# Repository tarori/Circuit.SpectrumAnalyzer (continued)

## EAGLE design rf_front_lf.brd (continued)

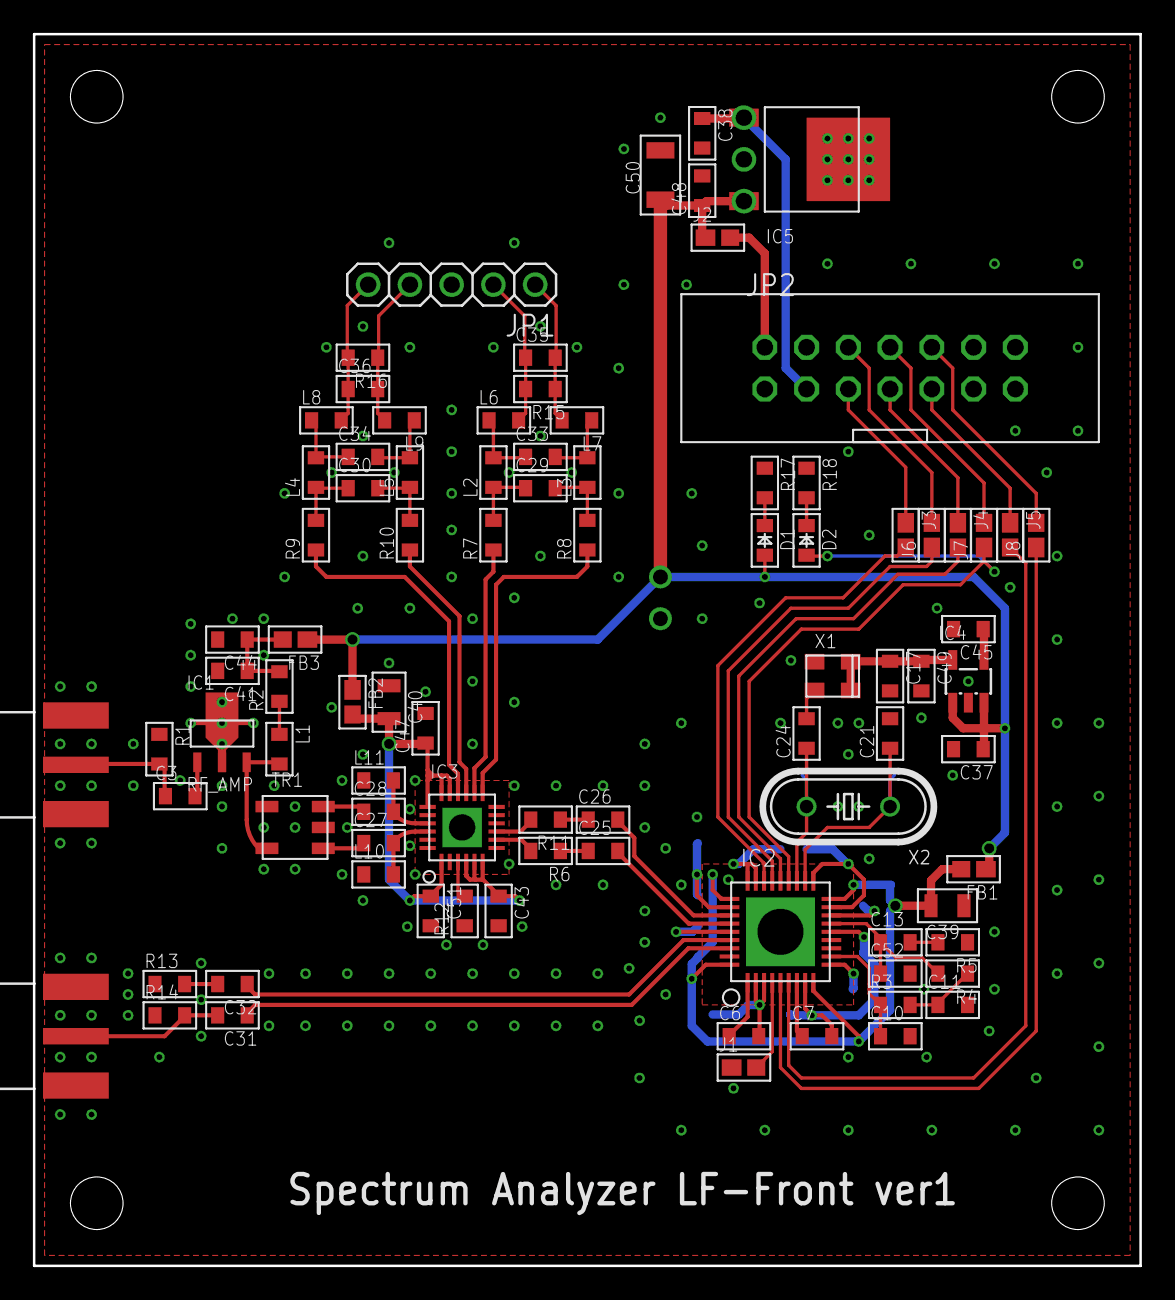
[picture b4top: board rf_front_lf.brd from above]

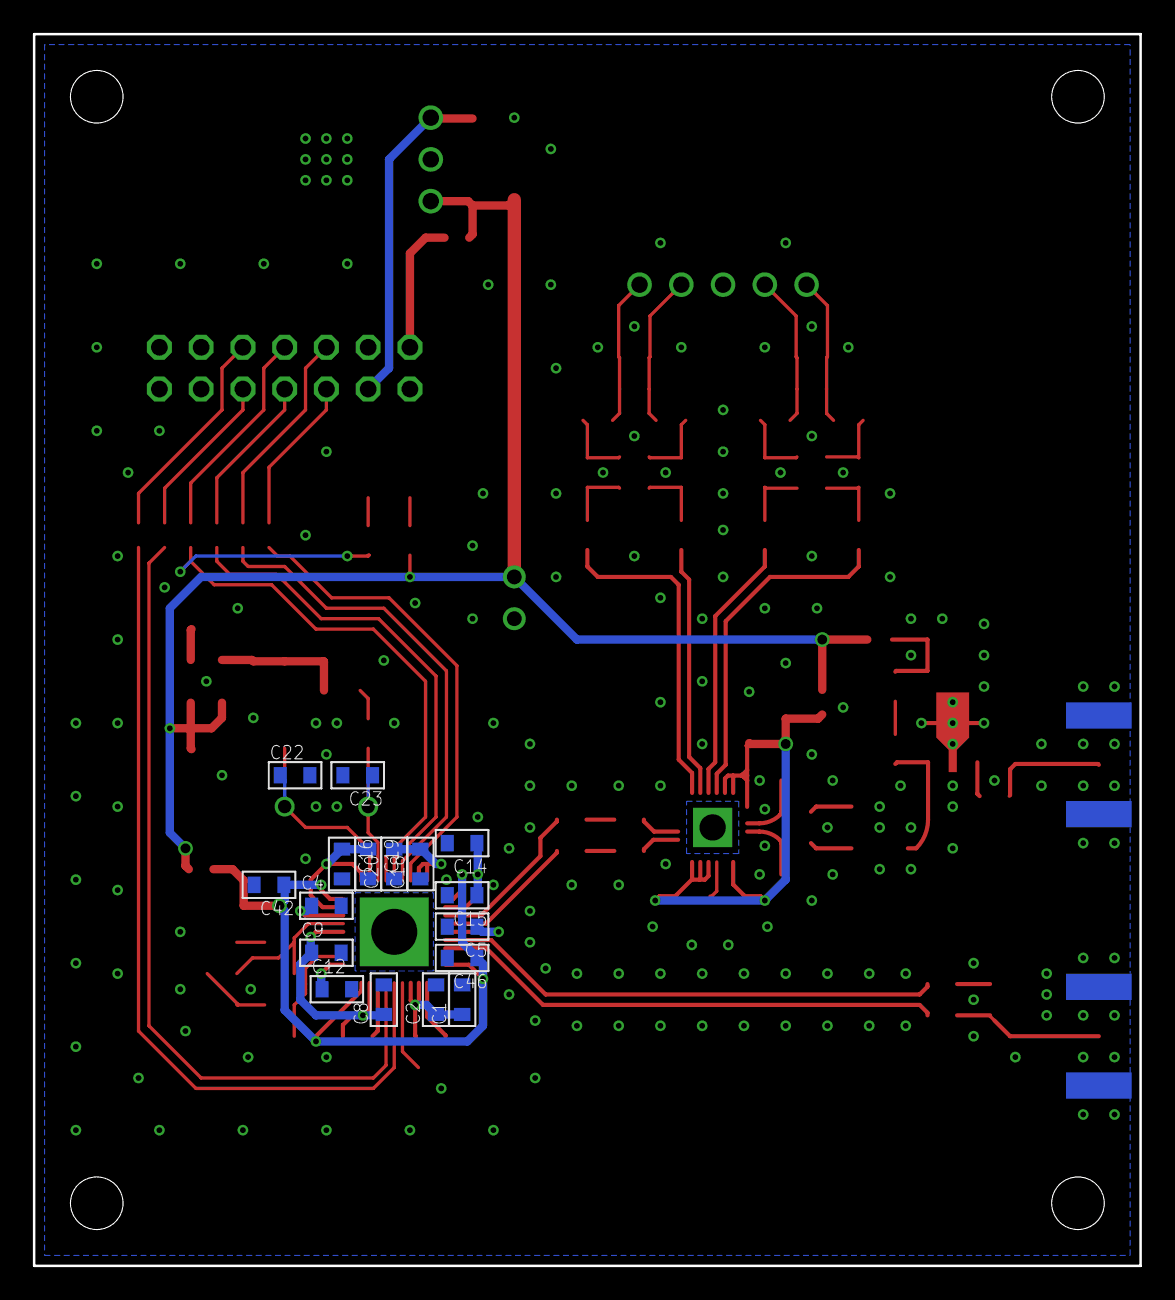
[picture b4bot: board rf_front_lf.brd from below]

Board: 4 copper layers, 67.3 x 74.9 mm, 112 parts (17 on the bottom side), 74 nets.

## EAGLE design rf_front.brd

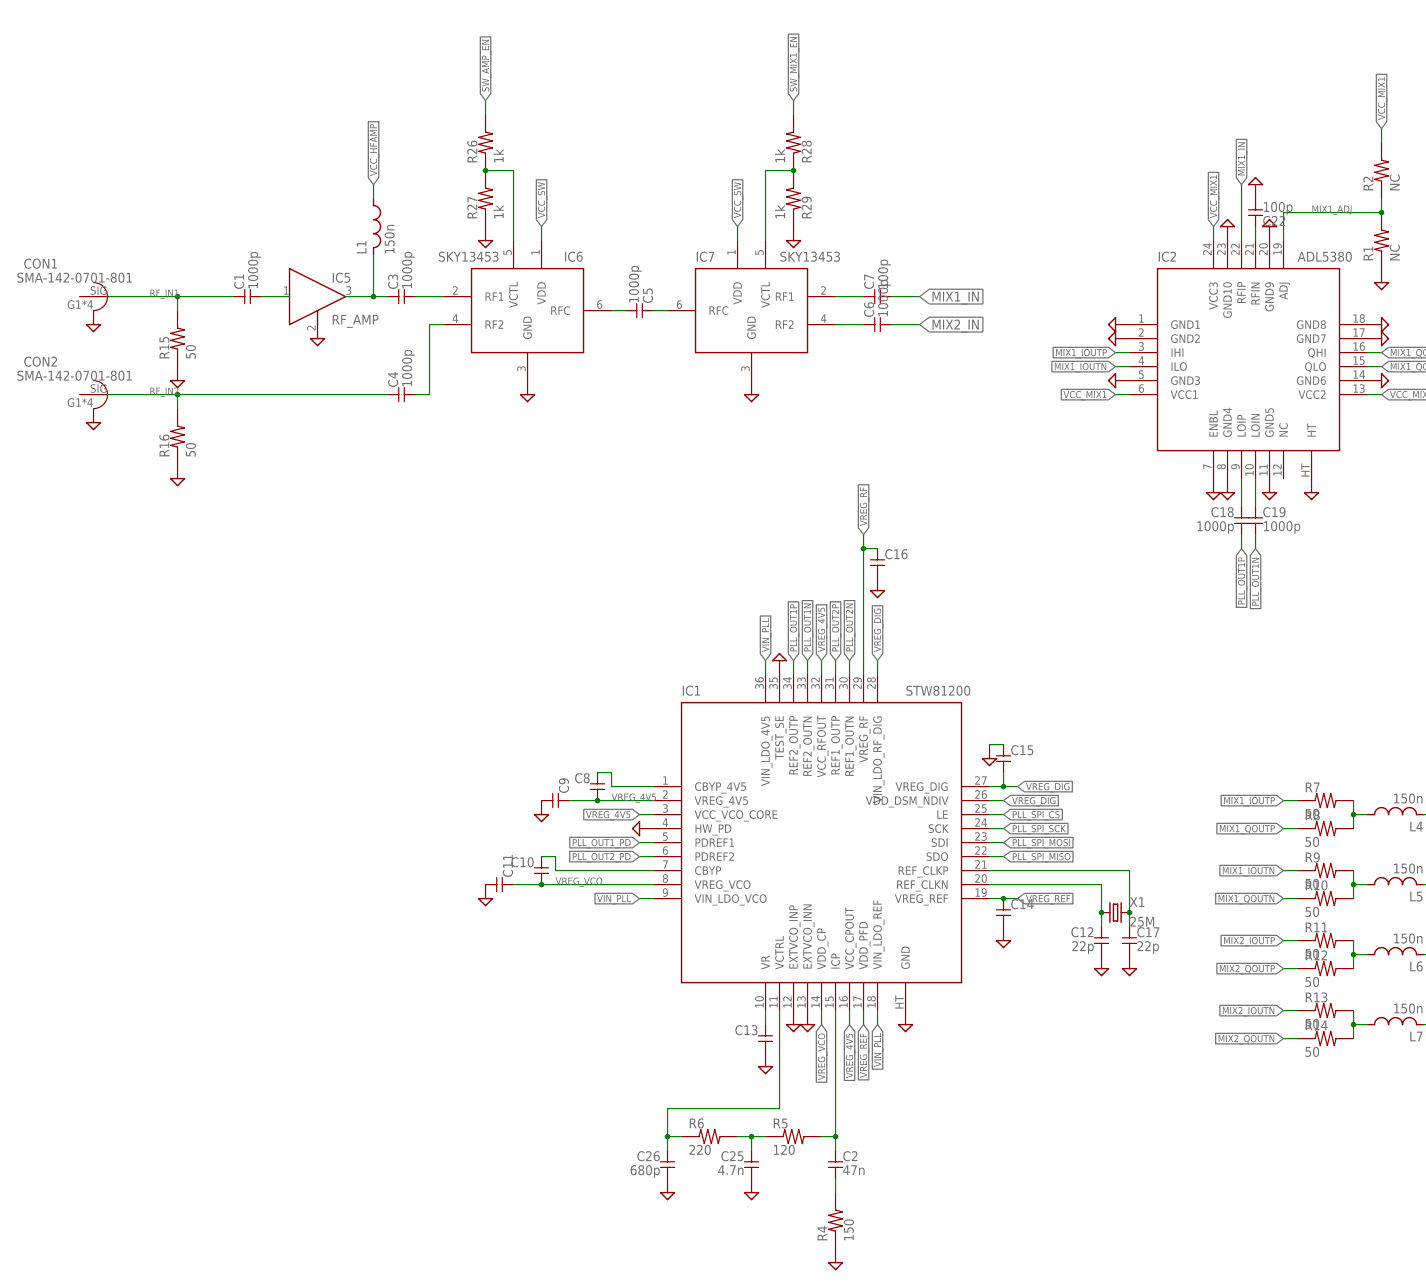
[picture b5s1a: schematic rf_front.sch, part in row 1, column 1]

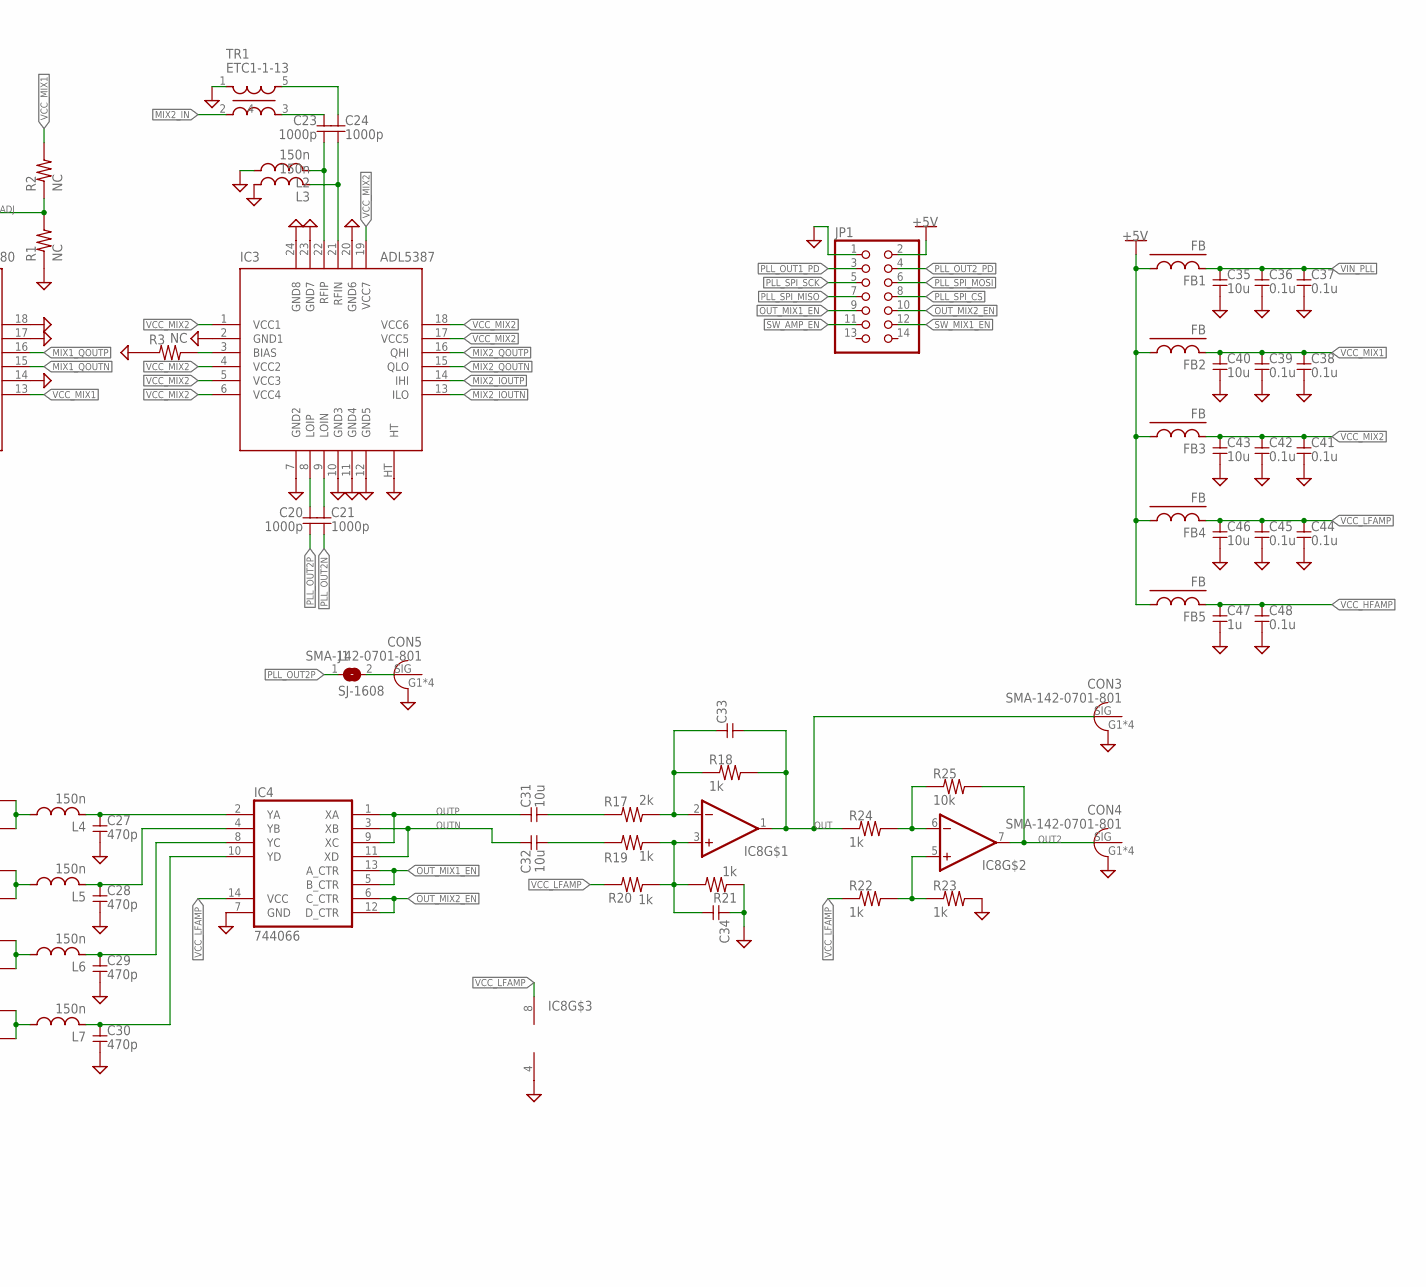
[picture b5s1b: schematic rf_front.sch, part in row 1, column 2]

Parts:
C1, C3, C4, C5, C6, C18, C19, C20, C21, C23, C24: 1000p; 1608
C2: 47n; 1608
C7, C22: 100p; 1608
C8, C9, C10, C11, C13, C14, C15, C16, C33, C34: C-1608; 1608
C12, C17: 22p; 1608
C25: 4.7n; 1608
C26: 680p; 1608
C27, C28, C29, C30: 470p; 1608
C31, C32, C35, C40, C43, C46: 10u; 2012
C36, C37, C38, C39, C41, C42, C44, C45, C48: 0.1u; 1608
C47: 1u; 1608
CON1, CON2, CON3, CON4, CON5: SMA-142-0701-801
FB1, FB2, FB3, FB4, FB5: FB; 1608-J
IC1: STW81200; VFQFPN36
IC2: ADL5380; LFCSP24
IC3: ADL5387; LFCSP24
IC4: 744066; SOP14
IC5: RF_AMP; SOT89
IC6, IC7: SKY13453
IC8: OPA-2-SOP; SOP8
J1: SJ-1608; 1608-J
JP1: PINHD-2X7; 2X07
L1, L2, L3, L4, L5, L6, L7: 150n; 1608
R1, R2, R3: NC; 1608
R4: 150; 1608
R5: 120; 1608
R6: 220; 1608
R7, R8, R9, R10, R11, R12, R13, R14, R15, R16: 50; 1608
R17: 2k; 1608
R18, R19, R20, R21, R22, R23, R24, R26, R27, R28, R29: 1k; 1608
R25: 10k; 1608
TR1: ETC1-1-13
X1: 25M; HC49/S

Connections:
+5V: FB1.1, FB2.1, FB3.1, FB4.1, FB5.1, JP1.2
GND: C9.2, C11.2, C12.2, C13.2, C14.2, C15.1, C16.2, C17.2, C22.2, C25.2, C26.2, C27.2, C28.2, C29.2, C30.2, C34.1, C35.2, C36.2, C37.2, C38.2, C39.2, C40.2, C41.2, C42.2, C43.2, C44.2, C45.2, C46.2, C47.2, C48.2, CON1.G1 (GND), CON1.G2 (GND), CON1.G3 (GND), CON1.G4 (GND), CON2.G1 (GND), CON2.G2 (GND), CON2.G3 (GND), CON2.G4 (GND), CON3.G1 (GND), CON3.G2 (GND), CON3.G3 (GND), CON3.G4 (GND), CON4.G1 (GND), CON4.G2 (GND), CON4.G3 (GND), CON4.G4 (GND), CON5.G1 (GND), CON5.G2 (GND), CON5.G3 (GND), CON5.G4 (GND), IC1.4 (HW_PD), IC1.12 (EXTVCO_INP), IC1.13 (EXTVCO_INN), IC1.35 (TEST_SE), IC1.HT (GND), IC2.1 (GND1), IC2.2 (GND2), IC2.5 (GND3), IC2.7 (ENBL), IC2.8 (GND4), IC2.11 (GND5), IC2.14 (GND6), IC2.17 (GND7), IC2.18 (GND8), IC2.20 (GND9), IC2.23 (GND10), IC2.HT, IC3.2 (GND1), IC3.7 (GND2), IC3.10 (GND3), IC3.11 (GND4), IC3.12 (GND5), IC3.20 (GND6), IC3.23 (GND7), IC3.24 (GND8), IC3.HT, IC4.7 (GND), IC5.2 (GND), IC6.3 (GND), IC7.3 (GND), IC8.4 (V-), JP1.1, L2.1, L3.1, R1.1, R3.1, R4.1, R15.1, R16.1, R21.1, R23.2, R27.1, R29.1, TR1.1
MIX1_ADJ: IC2.19 (ADJ), R1.2, R2.1
MIX1_IN: C7.2, IC2.22 (RFIP)
MIX1_IOUTN: IC2.4 (ILO), R9.1
MIX1_IOUTP: IC2.3 (IHI), R7.1
MIX1_QOUTN: IC2.15 (QLO), R10.1
MIX1_QOUTP: IC2.16 (QHI), R8.1
MIX2_IN: C6.2, TR1.2
MIX2_IOUTN: IC3.13 (ILO), R13.1
MIX2_IOUTP: IC3.14 (IHI), R11.1
MIX2_QOUTN: IC3.15 (QLO), R14.1
MIX2_QOUTP: IC3.16 (QHI), R12.1
unnamed: C1.2, IC5.1 (IN)
unnamed: C2.2, R4.2
unnamed: C2.1, IC1.15 (ICP), R5.2
unnamed: C3.1, IC5.3 (OUT), L1.2
unnamed: C25.1, R5.1, R6.2
unnamed: C4.2, IC6.4 (RF2)
unnamed: C3.2, IC6.2 (RF1)
unnamed: C5.2, IC6.6 (RFC)
unnamed: C5.1, IC7.6 (RFC)
unnamed: C6.1, IC7.4 (RF2)
unnamed: C7.1, IC7.2 (RF1)
unnamed: C13.1, IC1.10 (VR)
unnamed: C8.1, IC1.1 (CBYP_4V5)
unnamed: C12.1, IC1.20 (REF_CLKN), X1.1
unnamed: C10.1, IC1.7 (CBYP)
unnamed: C17.1, IC1.21 (REF_CLKP), X1.2
unnamed: C18.1, IC2.9 (LOIP)
unnamed: C19.1, IC2.10 (LOIN)
unnamed: IC3.3 (BIAS), R3.2
unnamed: C22.1, IC2.21 (RFIN)
unnamed: C20.1, IC3.8 (LOIP)
unnamed: C21.1, IC3.9 (LOIN)
unnamed: C24.2, IC3.21 (RFIN), L3.2
unnamed: C23.2, IC3.22 (RFIP), L2.2
unnamed: C23.1, TR1.3
unnamed: C24.1, TR1.5
unnamed: C26.1, IC1.11 (VCTRL), R6.1
unnamed: C30.1, IC4.10 (YD), L7.2
unnamed: C29.1, IC4.8 (YC), L6.2
unnamed: C28.1, IC4.4 (YB), L5.2
unnamed: C27.1, IC4.2 (YA), L4.2
unnamed: L4.1, R7.2, R8.2
unnamed: L5.1, R9.2, R10.2
unnamed: L6.1, R11.2, R12.2
unnamed: L7.1, R13.2, R14.2
unnamed: C34.2, IC8.3 (+IN), R19.2, R20.1, R21.2
unnamed: C33.1, IC8.2 (-IN), R17.2, R18.1
unnamed: C31.2, R17.1
unnamed: C32.2, R19.1
unnamed: IC8.5 (+IN), R22.2, R23.1
unnamed: CON5.SIG, J1.2
unnamed: IC8.6 (-IN), R24.2, R25.1
unnamed: IC6.5 (VCTL), R26.1, R27.2
unnamed: IC7.5 (VCTL), R28.1, R29.2
OUT: C33.2, CON3.SIG, IC8.1 (OUT), R18.2, R24.1
OUT2: CON4.SIG, IC8.7 (OUT), R25.2
OUTN: C32.1, IC4.3 (XB), IC4.11 (XD)
OUTP: C31.1, IC4.1 (XA), IC4.9 (XC)
OUT_MIX1_EN: IC4.5 (B_CTR), IC4.13 (A_CTR), JP1.9
OUT_MIX2_EN: IC4.6 (C_CTR), IC4.12 (D_CTR), JP1.10
PLL_OUT1N: C19.2, IC1.33 (REF2_OUTN)
PLL_OUT1P: C18.2, IC1.34 (REF2_OUTP)
PLL_OUT1_PD: IC1.5 (PDREF1), JP1.3
PLL_OUT2N: C21.2, IC1.30 (REF1_OUTN)
PLL_OUT2P: C20.2, IC1.31 (REF1_OUTP), J1.1
PLL_OUT2_PD: IC1.6 (PDREF2), JP1.4
PLL_SPI_CS: IC1.25 (LE), JP1.8
PLL_SPI_MISO: IC1.22 (SDO), JP1.7
PLL_SPI_MOSI: IC1.23 (SDI), JP1.6
PLL_SPI_SCK: IC1.24 (SCK), JP1.5
RF_IN1: C1.1, CON1.SIG, R15.2
RF_IN2: C4.1, CON2.SIG, R16.2
SW_AMP_EN: JP1.11, R26.2
SW_MIX1_EN: JP1.12, R28.2
VCC_HFAMP: C47.1, C48.1, FB5.2, L1.1
VCC_LFAMP: C44.1, C45.1, C46.1, FB4.2, IC4.14 (VCC), IC8.8 (V+), R20.2, R22.1
VCC_MIX1: C38.1, C39.1, C40.1, FB2.2, IC2.6 (VCC1), IC2.13 (VCC2), IC2.24 (VCC3), R2.2
VCC_MIX2: C41.1, C42.1, C43.1, FB3.2, IC3.1 (VCC1), IC3.4 (VCC2), IC3.5 (VCC3), IC3.6 (VCC4), IC3.17 (VCC5), IC3.18 (VCC6), IC3.19 (VCC7)
VCC_SW: IC6.1 (VDD), IC7.1 (VDD)
VIN_PLL: C35.1, C36.1, C37.1, FB1.2, IC1.9 (VIN_LDO_VCO), IC1.18 (VIN_LDO_REF), IC1.36 (VIN_LDO_4V5)
VREG_4V5: C8.2, C9.1, IC1.2 (VREG_4V5), IC1.3 (VCC_VCO_CORE), IC1.16 (VCC_CPOUT), IC1.32 (VCC_RFOUT)
VREG_DIG: C15.2, IC1.26 (VDD_DSM_NDIV), IC1.27 (VREG_DIG), IC1.28 (VIN_LDO_RF_DIG)
VREG_REF: C14.1, IC1.17 (VDD_PFD), IC1.19 (VREG_REF)
VREG_RF: C16.1, IC1.29 (VREG_RF)
VREG_VCO: C10.2, C11.1, IC1.8 (VREG_VCO), IC1.14 (VDD_CP)

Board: 4 copper layers, 106 parts (0 on the bottom side), 88 nets, no tracks yet.

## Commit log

2023-05-12 HFできた
2024-05-24 マイコンも載せる
2024-05-25 ほぼ完成
2026-05-29 STw81200
2026-05-31 Add RF Amp Test
2026-05-31 PLLをLMX2572に
